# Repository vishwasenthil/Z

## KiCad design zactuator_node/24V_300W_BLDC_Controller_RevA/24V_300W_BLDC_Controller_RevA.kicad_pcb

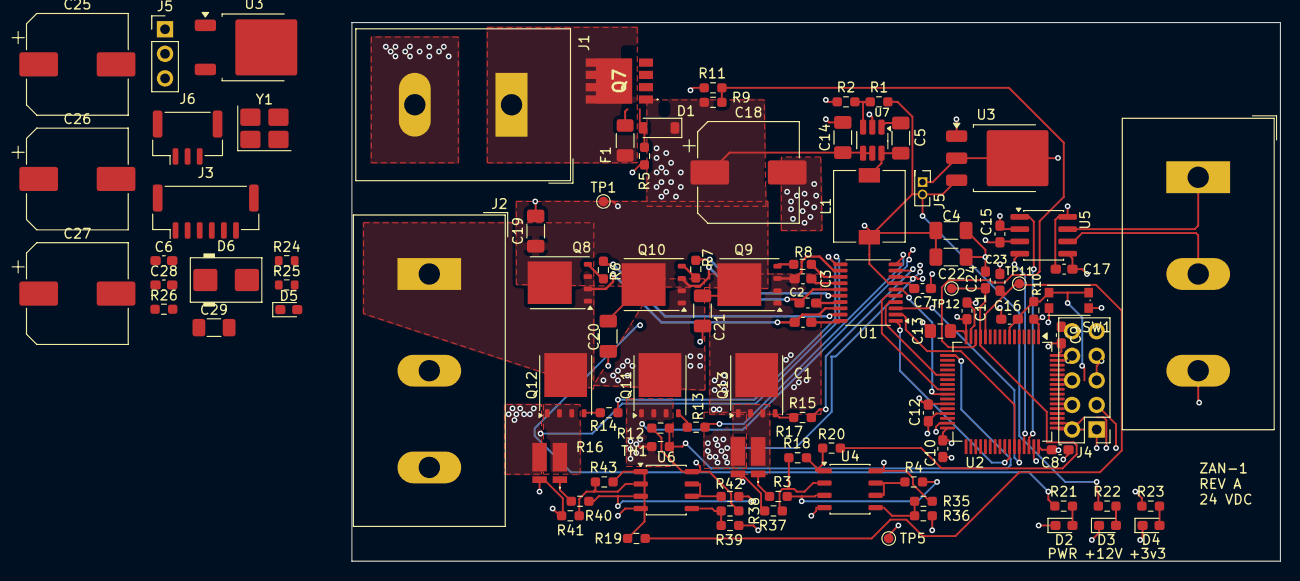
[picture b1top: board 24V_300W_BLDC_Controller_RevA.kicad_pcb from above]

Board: 4 copper layers, 96.0 x 55.7 mm, 102 parts (0 on the bottom side), 71 nets.

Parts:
C1, C2, C3, C6, C8, C9, C10, C11, C12, C15, C16, C17, C28: 100n; C_0603_1608Metric_Pad1.08x0.95mm_HandSolder
C4: 10u; C_1206_3216Metric_Pad1.33x1.80mm_HandSolder
C5: 100n; C_1206_3216Metric_Pad1.33x1.80mm_HandSolder
C7: 10u; C_0603_1608Metric_Pad1.08x0.95mm_HandSolder
C13: 10u; C_0805_2012Metric_Pad1.18x1.45mm_HandSolder
C14, C29: 2.2u; C_1206_3216Metric_Pad1.33x1.80mm_HandSolder
C18, C25, C26, C27: 150u; CP_Elec_10x10
C19, C20, C21: C_Small; C_1206_3216Metric_Pad1.33x1.80mm_HandSolder
C22: 22u; C_1206_3216Metric_Pad1.33x1.80mm_HandSolder
C23, C24: C; C_0603_1608Metric_Pad1.08x0.95mm_HandSolder
D1: D_Zener; D_SOD-123
D2, D3, D4, D5: LED; LED_0603_1608Metric_Pad1.05x0.95mm_HandSolder
D6: SMBJ36A; D_SMB
F1: Fuse; R_1206_3216Metric_Pad1.30x1.75mm_HandSolder
J1: Screw_Terminal_01x02; TerminalBlock_Dinkle_DT-55-B01X-02_P10.00mm
J2, J3: Screw_Terminal_01x03; TerminalBlock_Dinkle_DT-55-B01X-03_P10.00mm
J3#2: Conn_01x06; JST_GH_BM06B-GHS-TBT_1x06-1MP_P1.25mm_Vertical
J4: Conn_02x05_Counter_Clockwise; PinHeader_2x05_P2.54mm_Vertical
J5: Conn_01x03_Pin; PinHeader_1x03_P2.54mm_Vertical
J5#2: Conn_02x01; PinHeader_2x01_P1.27mm_Vertical
J6: Conn_01x03; JST_GH_BM03B-GHS-TBT_1x03-1MP_P1.25mm_Vertical
L1: 33u; L_7.3x7.3_H4.5
Q7: PMOS; XPH4R714MC
Q8, Q9, Q10, Q11, Q12, Q13: BSC061N08NS5; TDSON-8-1
R1: 140k; R_0603_1608Metric_Pad0.98x0.95mm_HandSolder
R2, R10, R11, R12, R21, R35, R36, R38, R39: 10k; R_0603_1608Metric_Pad0.98x0.95mm_HandSolder
R3, R37, R40, R41: 1k; R_0603_1608Metric_Pad0.98x0.95mm_HandSolder
R4, R18, R42, R43: 30k; R_0603_1608Metric_Pad0.98x0.95mm_HandSolder
R5: 100k; R_0603_1608Metric_Pad0.98x0.95mm_HandSolder
R6, R7, R8, R13, R14, R15: 10; R_0603_1608Metric_Pad0.98x0.95mm_HandSolder
R9: 120k; R_0603_1608Metric_Pad0.98x0.95mm_HandSolder
R16, R17: LRMAP1216A-1L0FT3; LRMAP1216A1L0FT3
R19, R20: R; R_0603_1608Metric_Pad0.98x0.95mm_HandSolder
R22: 5.1k; R_0603_1608Metric_Pad0.98x0.95mm_HandSolder
R23: 680; R_0603_1608Metric_Pad0.98x0.95mm_HandSolder
R24: 1k; R_0603_1608Metric
R25: 10k; R_0603_1608Metric
R26: 120; R_0603_1608Metric_Pad0.98x0.95mm_HandSolder
SW1: SW_Push; SW_Push_1P1T_NO_CK_KMR2
TH1: 10k; R_0603_1608Metric_Pad0.98x0.95mm_HandSolder
TP1, TP5, TP11, TP12: TestPoint; TestPoint_Pad_D1.0mm
U1: DRV8300DIPWR; TSSOP-20_4.4x6.5mm_P0.65mm
U2: STM32G474RETx; LQFP-64_10x10mm_P0.5mm
U3: LM1117DT-3.3; TO-252-3_TabPin2
U3#2: TLV76133KVUR; TO-252-2
U4, U6: TLV9062; JEITA_SOIC-8_3.9x4.9mm_P1.27mm
U5: PTCAN3403DRQ1; SOIC-8_3.9x4.9mm_P1.27mm
U7: SOT-23-6_Handsoldering
Y1: Crystal; Crystal_SMD_3225-4Pin_3.2x2.5mm_HandSoldering

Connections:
+3.3V: C6.1, C8.1, C9.1, C10.1, C11.1, C12.1, C13.1, C15.2, C17.1, C29.1, J3#2.1, J4.1, J5.1, J5#2.1, R10.1, R12.1, R23.2, R35.1, R38.1, U2.1 (VBAT), U2.16 (VDD), U2.28 (VREF+), U2.29 (VDDA), U2.32 (VDD), U2.48 (VDD), U2.64 (VDD), U3.2 (VO), U3#2.2 (VO), U4.8 (V+), U5.3 (VCC), U5.5 (VIO), U6.8 (V+)
+24V: D6.1 (K), F1.1, J1.1
/+12V: C4.1, C7.1, C22.1, C28.2, J5.3, J5#2.2, L1.2, R1.1, R22.2, U1.7 (GVDD), U3.3 (VI), U3#2.3 (VI)
/+24V_BUS: C14.1, C18.1, C19.1, C20.1, C21.1, C25.1, C26.1, C27.1, D1.1 (K), Q7.3 (S), Q8.5 (D), Q9.5 (D), Q10.5 (D), R9.1, R21.2, TP1.1 (1_1), U7.4 (EN), U7.5 (VIN)
/CANH: J3.1, J6.1, R26.1, U5.7 (CANH)
/CANL: J3.2, J6.2, R26.2, U5.6 (CANL)
/Encoder_CS: J3#2.3, U2.18 (PA4)
/Encoder_MISO: J3#2.4, U2.57 (PB4)
/Encoder_MOSI: J3#2.5, U2.58 (PB5)
/Encoder_SCK: J3#2.2, U2.56 (PB3)
/FDCAN1_RX: U2.45 (PA11), U5.4 (RXD)
/FDCAN1_TX: U2.46 (PA12), U5.1 (TXD)
/GHA: R6.1, U1.19 (GHA)
/GHB: R7.1, U1.16 (GHB)
/GHC: R8.1, U1.13 (GHC)
/GLA: R14.1, U1.11 (GLA)
/GLB: R13.1, U1.10 (GLB)
/GLC: R15.1, U1.9 (GLC)
/INHA: U1.1 (INHA), U2.42 (PA8)
/INHB: U1.2 (INHB), U2.43 (PA9)
/INHC: U1.3 (INHC), U2.44 (PA10)
/INLA: U1.4 (INLA), U2.21 (PA7)
/INLB: U1.5 (INLB), U2.24 (PB0)
/INLC: U1.6 (INLC), U2.25 (PB1)
/I_SENSE_A: C23.1, R19.2, TP11.1 (1_1), U2.12 (PA0)
/I_SENSE_C: C24.1, R20.2, TP12.1 (1_1), U2.13 (PA1)
/NRST: C16.2, J4.10, R10.2, SW1.2, U2.7 (PG10)
/Phase_A: C1.2, J2.1, Q8.1 (S), Q8.2 (S), Q8.3 (S), Q12.5 (D), U1.18 (SHA)
/Phase_B: C2.2, J2.2, Q10.1 (S), Q10.2 (S), Q10.3 (S), Q11.5 (D), U1.15 (SHB)
/Phase_C: C3.2, J2.3, Q9.1 (S), Q9.2 (S), Q9.3 (S), Q13.5 (D), U1.12 (SHC)
/SWCLK: J4.4, U2.50 (PA14)
/SWDIO: J4.2, U2.49 (PA13)
/T_SENSE: R12.2, TH1.1, U2.17 (PA3)
/VSHUNT_1: R16.1 (VSENSE_1), R40.1
/VSHUNT_2: R3.1, R17.1 (VSENSE_1)
/V_BUS_SENSE: R9.2, R11.1, U2.14 (PA2)
GND: C4.2, C6.2, C7.2, C8.2, C9.2, C10.2, C11.2, C12.2, C13.2, C14.2, C15.1, C16.1, C17.2, C18.2, C19.2, C20.2, C21.2, C22.2, C23.2, C24.2, C25.2, C26.2, C27.2, C29.2, D2.1 (K), D3.1 (K), D4.1 (K), D5.1 (K), D6.2 (A), J1.2, J3.3, J3#2.6, J4.3, J4.5, J4.9, J5.2, J6.3, Q11.1 (S), Q11.2 (S), Q11.3 (S), R2.2, R5.1, R11.2, R16.3 (CURRENT_2), R16.4 (VSENSE_2), R17.3 (CURRENT_2), R17.4 (VSENSE_2), R25.2, R36.2, R37.2, R39.2, R41.2, SW1.1, TH1.2, TP5.1 (1_1), U1.8 (GND), U2.15 (VSS), U2.27 (VSSA), U2.31 (VSS), U2.47 (VSS), U2.63 (VSS), U3.1 (GND), U3#2.1 (GND), U4.4 (V-), U5.2 (GND), U5.8 (STB), U6.4 (V-), U7.2 (GND), Y1.2 (G), Y1.4 (G)
unnamed: D1.2 (A), Q7.2 (G), R5.2
unnamed: D2.2 (A), R21.1
unnamed: D3.2 (A), R22.1
unnamed: D4.2 (A), R23.1
unnamed: D5.2 (A), R24.2
unnamed: F1.2, Q7.1 (D)
unnamed: Q8.4 (G), R6.2
unnamed: Q9.4 (G), R8.2
unnamed: Q10.4 (G), R7.2
unnamed: Q11.4 (G), R13.2
unnamed: Q12.4 (G), R14.2
unnamed: Q13.4 (G), R15.2
unnamed: Q12.1 (S), Q12.2 (S), Q12.3 (S), R16.2 (CURRENT_1)
unnamed: Q13.1 (S), Q13.2 (S), Q13.3 (S), R17.2 (CURRENT_1)
unnamed: R18.1, R20.1, U4.1
unnamed: R19.1, R43.1, U6.1
unnamed: C1.1, U1.20 (BSTA)
unnamed: C2.1, U1.17 (BSTB)
unnamed: C3.1, U1.14 (BSTC)
unnamed: R25.1, U2.61 (PB8)
unnamed: R24.1, U2.37 (PB15)
unnamed: U2.5 (PF0), Y1.1
unnamed: U2.6 (PF1), Y1.3
unnamed: R3.2, R4.1, U4.3 (+)
unnamed: R18.2, R37.1, U4.2 (-)
unnamed: R35.2, R36.1, U4.5 (+)
unnamed: R4.2, U4.6 (-), U4.7
unnamed: R40.2, R42.1, U6.3 (+)
unnamed: R41.1, R43.2, U6.2 (-)
unnamed: R38.2, R39.1, U6.5 (+)
unnamed: R42.2, U6.6 (-), U6.7
unnamed: C5.1, U7.1 (CB)
unnamed: R1.2, R2.1, U7.3 (FB)
unnamed: C5.2, L1.1, U7.6 (SW)

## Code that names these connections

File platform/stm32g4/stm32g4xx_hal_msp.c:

/* USER CODE BEGIN Header */
/**
  ******************************************************************************
  * @file         stm32g4xx_hal_msp.c
  * @brief        This file provides code for the MSP Initialization
  *               and de-Initialization codes.
  ******************************************************************************
  * @attention
  *
  * Copyright (c) 2026 STMicroelectronics.
  * All rights reserved.
  *
  * This software is licensed under terms that can be found in the LICENSE file
  * in the root directory of this software component.
  * If no LICENSE file comes with this software, it is provided AS-IS.
  *
  ******************************************************************************
  */
/* USER CODE END Header */

/* Includes ------------------------------------------------------------------*/
#include "board_config.h"
/* USER CODE BEGIN Includes */

/* USER CODE END Includes */

/* Private typedef -----------------------------------------------------------*/
/* USER CODE BEGIN TD */

/* USER CODE END TD */

/* Private define ------------------------------------------------------------*/
/* USER CODE BEGIN Define */

/* USER CODE END Define */

/* Private macro -------------------------------------------------------------*/
/* USER CODE BEGIN Macro */

/* USER CODE END Macro */

/* Private variables ---------------------------------------------------------*/
/* USER CODE BEGIN PV */

/* USER CODE END PV */

/* Private function prototypes -----------------------------------------------*/
/* USER CODE BEGIN PFP */

/* USER CODE END PFP */

/* External functions --------------------------------------------------------*/
/* USER CODE BEGIN ExternalFunctions */

/* USER CODE END ExternalFunctions */

/* USER CODE BEGIN 0 */

/* USER CODE END 0 */

void HAL_TIM_MspPostInit(TIM_HandleTypeDef *htim);
                    /**
  * Initializes the Global MSP.
  */
void HAL_MspInit(void)
{

  /* USER CODE BEGIN MspInit 0 */

  /* USER CODE END MspInit 0 */

  __HAL_RCC_SYSCFG_CLK_ENABLE();
  __HAL_RCC_PWR_CLK_ENABLE();

  /* System interrupt init*/

  /** Disable the internal Pull-Up in Dead Battery pins of UCPD peripheral
  */
  HAL_PWREx_DisableUCPDDeadBattery();

  /* USER CODE BEGIN MspInit 1 */

  /* USER CODE END MspInit 1 */
}

/**
  * @brief ADC MSP Initialization
  * This function configures the hardware resources used in this example
  * @param hadc: ADC handle pointer
  * @retval None
  */
void HAL_ADC_MspInit(ADC_HandleTypeDef* hadc)
{
  GPIO_InitTypeDef GPIO_InitStruct = {0};
  RCC_PeriphCLKInitTypeDef PeriphClkInit = {0};
  if(hadc->Instance==ADC1)
  {
    /* USER CODE BEGIN ADC1_MspInit 0 */

    /* USER CODE END ADC1_MspInit 0 */

  /** Initializes the peripherals clocks
  */
    PeriphClkInit.PeriphClockSelection = RCC_PERIPHCLK_ADC12;
    PeriphClkInit.Adc12ClockSelection = RCC_ADC12CLKSOURCE_SYSCLK;
    if (HAL_RCCEx_PeriphCLKConfig(&PeriphClkInit) != HAL_OK)
    {
      Error_Handler();
    }

    /* Peripheral clock enable */
    __HAL_RCC_ADC12_CLK_ENABLE();

    __HAL_RCC_GPIOA_CLK_ENABLE();
    /**ADC1 GPIO Configuration
    PA0     ------> ADC1_IN1
    PA2     ------> ADC1_IN3
    PA3     ------> ADC1_IN4
    */
    GPIO_InitStruct.Pin = I_SENSE_A_Pin|V_BUS_SENSE_Pin|T_SENSE_Pin;
    GPIO_InitStruct.Mode = GPIO_MODE_ANALOG;
    GPIO_InitStruct.Pull = GPIO_NOPULL;
    HAL_GPIO_Init(GPIOA, &GPIO_InitStruct);

    /* USER CODE BEGIN ADC1_MspInit 1 */

    /* USER CODE END ADC1_MspInit 1 */

  }

}

/**
  * @brief ADC MSP De-Initialization
  * This function freeze the hardware resources used in this example
  * @param hadc: ADC handle pointer
  * @retval None
  */
void HAL_ADC_MspDeInit(ADC_HandleTypeDef* hadc)
{
  if(hadc->Instance==ADC1)
  {
    /* USER CODE BEGIN ADC1_MspDeInit 0 */

    /* USER CODE END ADC1_MspDeInit 0 */
    /* Peripheral clock disable */
    __HAL_RCC_ADC12_CLK_DISABLE();

    /**ADC1 GPIO Configuration
    PA0     ------> ADC1_IN1
    PA2     ------> ADC1_IN3
    PA3     ------> ADC1_IN4
    */
    HAL_GPIO_DeInit(GPIOA, I_SENSE_A_Pin|V_BUS_SENSE_Pin|T_SENSE_Pin);

    /* USER CODE BEGIN ADC1_MspDeInit 1 */

    /* USER CODE END ADC1_MspDeInit 1 */
  }

}

/**
  * @brief FDCAN MSP Initialization
  * This function configures the hardware resources used in this example
  * @param hfdcan: FDCAN handle pointer
  * @retval None
  */
void HAL_FDCAN_MspInit(FDCAN_HandleTypeDef* hfdcan)
{
  GPIO_InitTypeDef GPIO_InitStruct = {0};
  RCC_PeriphCLKInitTypeDef PeriphClkInit = {0};
  if(hfdcan->Instance==FDCAN1)
  {
    /* USER CODE BEGIN FDCAN1_MspInit 0 */

    /* USER CODE END FDCAN1_MspInit 0 */

  /** Initializes the peripherals clocks
  */
    PeriphClkInit.PeriphClockSelection = RCC_PERIPHCLK_FDCAN;
    PeriphClkInit.FdcanClockSelection = RCC_FDCANCLKSOURCE_PCLK1;
    if (HAL_RCCEx_PeriphCLKConfig(&PeriphClkInit) != HAL_OK)
    {
      Error_Handler();
    }

    /* Peripheral clock enable */
    __HAL_RCC_FDCAN_CLK_ENABLE();

    __HAL_RCC_GPIOA_CLK_ENABLE();
    /**FDCAN1 GPIO Configuration
    PA11     ------> FDCAN1_RX
    PA12     ------> FDCAN1_TX
    */
    GPIO_InitStruct.Pin = GPIO_PIN_11|GPIO_PIN_12;
    GPIO_InitStruct.Mode = GPIO_MODE_AF_PP;
    GPIO_InitStruct.Pull = GPIO_NOPULL;
    GPIO_InitStruct.Speed = GPIO_SPEED_FREQ_LOW;
    GPIO_InitStruct.Alternate = GPIO_AF9_FDCAN1;
    HAL_GPIO_Init(GPIOA, &GPIO_InitStruct);

    /* USER CODE BEGIN FDCAN1_MspInit 1 */

    /* USER CODE END FDCAN1_MspInit 1 */

  }

}

/**
  * @brief FDCAN MSP De-Initialization
  * This function freeze the hardware resources used in this example
  * @param hfdcan: FDCAN handle pointer
  * @retval None
  */
void HAL_FDCAN_MspDeInit(FDCAN_HandleTypeDef* hfdcan)
{
  if(hfdcan->Instance==FDCAN1)
  {
    /* USER CODE BEGIN FDCAN1_MspDeInit 0 */

    /* USER CODE END FDCAN1_MspDeInit 0 */
    /* Peripheral clock disable */
    __HAL_RCC_FDCAN_CLK_DISABLE();

    /**FDCAN1 GPIO Configuration
    PA11     ------> FDCAN1_RX
    PA12     ------> FDCAN1_TX
    */
    HAL_GPIO_DeInit(GPIOA, GPIO_PIN_11|GPIO_PIN_12);

    /* USER CODE BEGIN FDCAN1_MspDeInit 1 */

    /* USER CODE END FDCAN1_MspDeInit 1 */
  }

}

/**
  * @brief TIM_PWM MSP Initialization
  * This function configures the hardware resources used in this example
  * @param htim_pwm: TIM_PWM handle pointer
  * @retval None
  */
void HAL_TIM_PWM_MspInit(TIM_HandleTypeDef* htim_pwm)
{
  if(htim_pwm->Instance==TIM1)
  {
    /* USER CODE BEGIN TIM1_MspInit 0 */

    /* USER CODE END TIM1_MspInit 0 */
    /* Peripheral clock enable */
    __HAL_RCC_TIM1_CLK_ENABLE();
    /* USER CODE BEGIN TIM1_MspInit 1 */

    /* USER CODE END TIM1_MspInit 1 */

  }

}

void HAL_TIM_MspPostInit(TIM_HandleTypeDef* htim)
{
  GPIO_InitTypeDef GPIO_InitStruct = {0};
  if(htim->Instance==TIM1)
  {
    /* USER CODE BEGIN TIM1_MspPostInit 0 */

    /* USER CODE END TIM1_MspPostInit 0 */

    __HAL_RCC_GPIOA_CLK_ENABLE();
    __HAL_RCC_GPIOB_CLK_ENABLE();
    /**TIM1 GPIO Configuration
    PA7     ------> TIM1_CH1N
    PB0     ------> TIM1_CH2N
    PB1     ------> TIM1_CH3N
    PA8     ------> TIM1_CH1
    PA9     ------> TIM1_CH2
    PA10     ------> TIM1_CH3
    */
    GPIO_InitStruct.Pin = PWM_UL_Pin|PWM_UH_Pin|PWM_VH_Pin|PWM_WH_Pin;
    GPIO_InitStruct.Mode = GPIO_MODE_AF_PP;
    GPIO_InitStruct.Pull = GPIO_NOPULL;
    GPIO_InitStruct.Speed = GPIO_SPEED_FREQ_LOW;
    GPIO_InitStruct.Alternate = GPIO_AF6_TIM1;
    HAL_GPIO_Init(GPIOA, &GPIO_InitStruct);

    GPIO_InitStruct.Pin = PWM_VL_Pin|PWM_WL_Pin;
    GPIO_InitStruct.Mode = GPIO_MODE_AF_PP;
    GPIO_InitStruct.Pull = GPIO_NOPULL;
    GPIO_InitStruct.Speed = GPIO_SPEED_FREQ_LOW;
    GPIO_InitStruct.Alternate = GPIO_AF6_TIM1;
    HAL_GPIO_Init(GPIOB, &GPIO_InitStruct);

    /* USER CODE BEGIN TIM1_MspPostInit 1 */

    /* USER CODE END TIM1_MspPostInit 1 */
  }

}
/**
  * @brief TIM_PWM MSP De-Initialization
  * This function freeze the hardware resources used in this example
  * @param htim_pwm: TIM_PWM handle pointer
  * @retval None
  */
void HAL_TIM_PWM_MspDeInit(TIM_HandleTypeDef* htim_pwm)
{
  if(htim_pwm->Instance==TIM1)
  {
    /* USER CODE BEGIN TIM1_MspDeInit 0 */

    /* USER CODE END TIM1_MspDeInit 0 */
    /* Peripheral clock disable */
    __HAL_RCC_TIM1_CLK_DISABLE();
    /* USER CODE BEGIN TIM1_MspDeInit 1 */

    /* USER CODE END TIM1_MspDeInit 1 */
  }

}

/* USER CODE BEGIN 1 */

/* USER CODE END 1 */
